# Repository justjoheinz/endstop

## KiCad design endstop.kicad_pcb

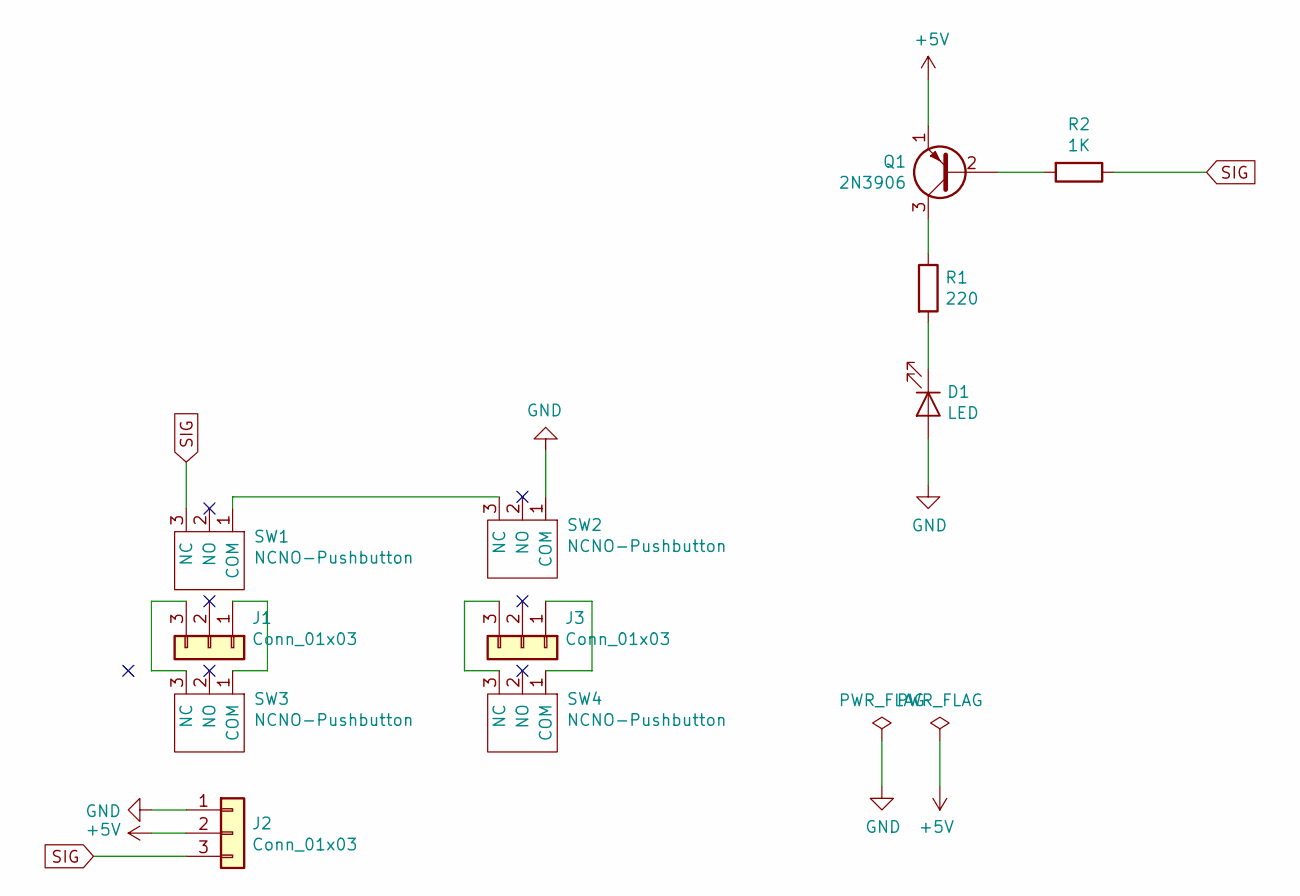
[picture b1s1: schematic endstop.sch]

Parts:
D1: LED; LED_D5.0mm
J1, J3: Conn_01x03; TerminalBlock_MetzConnect_Type101_RT01603HBWC_1x03_P5.08mm_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
J2: Conn_01x03; TerminalBlock_MetzConnect_Type094_RT03503HBLU_1x03_P5.00mm_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
Q1: 2N3906; TO-92_Inline
R1: 220; R_Axial_DIN0207_L6.3mm_D2.5mm_P7.62mm_Horizontal
R2: 1K; R_Axial_DIN0207_L6.3mm_D2.5mm_P7.62mm_Horizontal
SW1, SW2, SW3, SW4: NCNO-Pushbutton; SIP-3

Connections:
+5V: J2.2, Q1.1 (E)
GND: D1.2 (A), J2.1, SW2.1 (COM)
unnamed: D1.1 (K), R1.2
unnamed: J1.1, SW3.1 (COM)
unnamed: J1.3, SW3.3 (NC)
unnamed: J3.1, SW4.1 (COM)
unnamed: J3.3, SW4.3 (NC)
unnamed: Q1.2 (B), R2.2
unnamed: Q1.3 (C), R1.1
unnamed: SW1.1 (COM), SW2.3 (NC)
SIG: J2.3, R2.1, SW1.3 (NC)

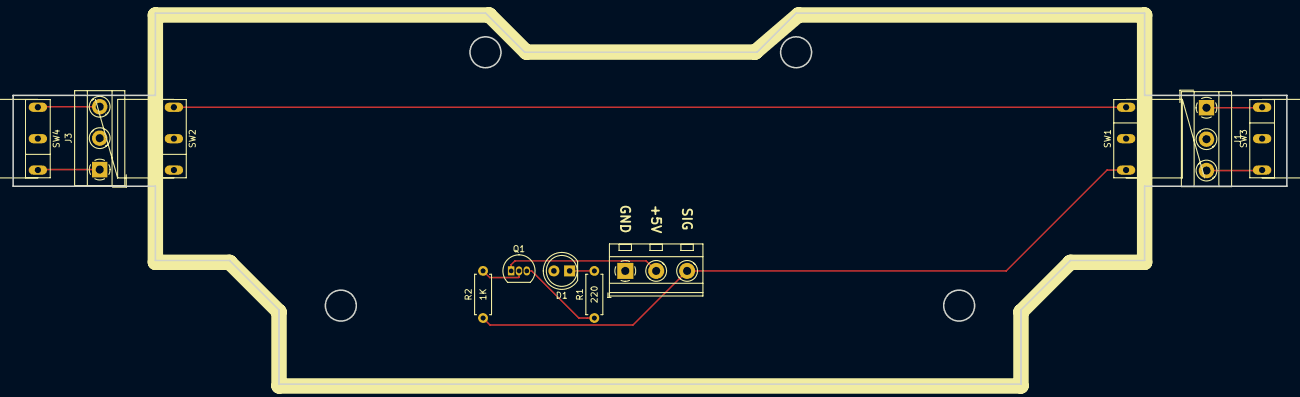
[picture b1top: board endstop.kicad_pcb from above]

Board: 2 copper layers, 206.0 x 60.0 mm, 17 parts (0 on the bottom side), 11 nets.

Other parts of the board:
MOUSEBITE1mm, MOUSEBITE1mm#2, MOUSEBITE1mm#3, MOUSEBITE1mm#4, MOUSEBITE1mm#5, MOUSEBITE1mm#6: VAL**; MOUSEBITE1mm

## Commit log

2020-05-15 Initial version
